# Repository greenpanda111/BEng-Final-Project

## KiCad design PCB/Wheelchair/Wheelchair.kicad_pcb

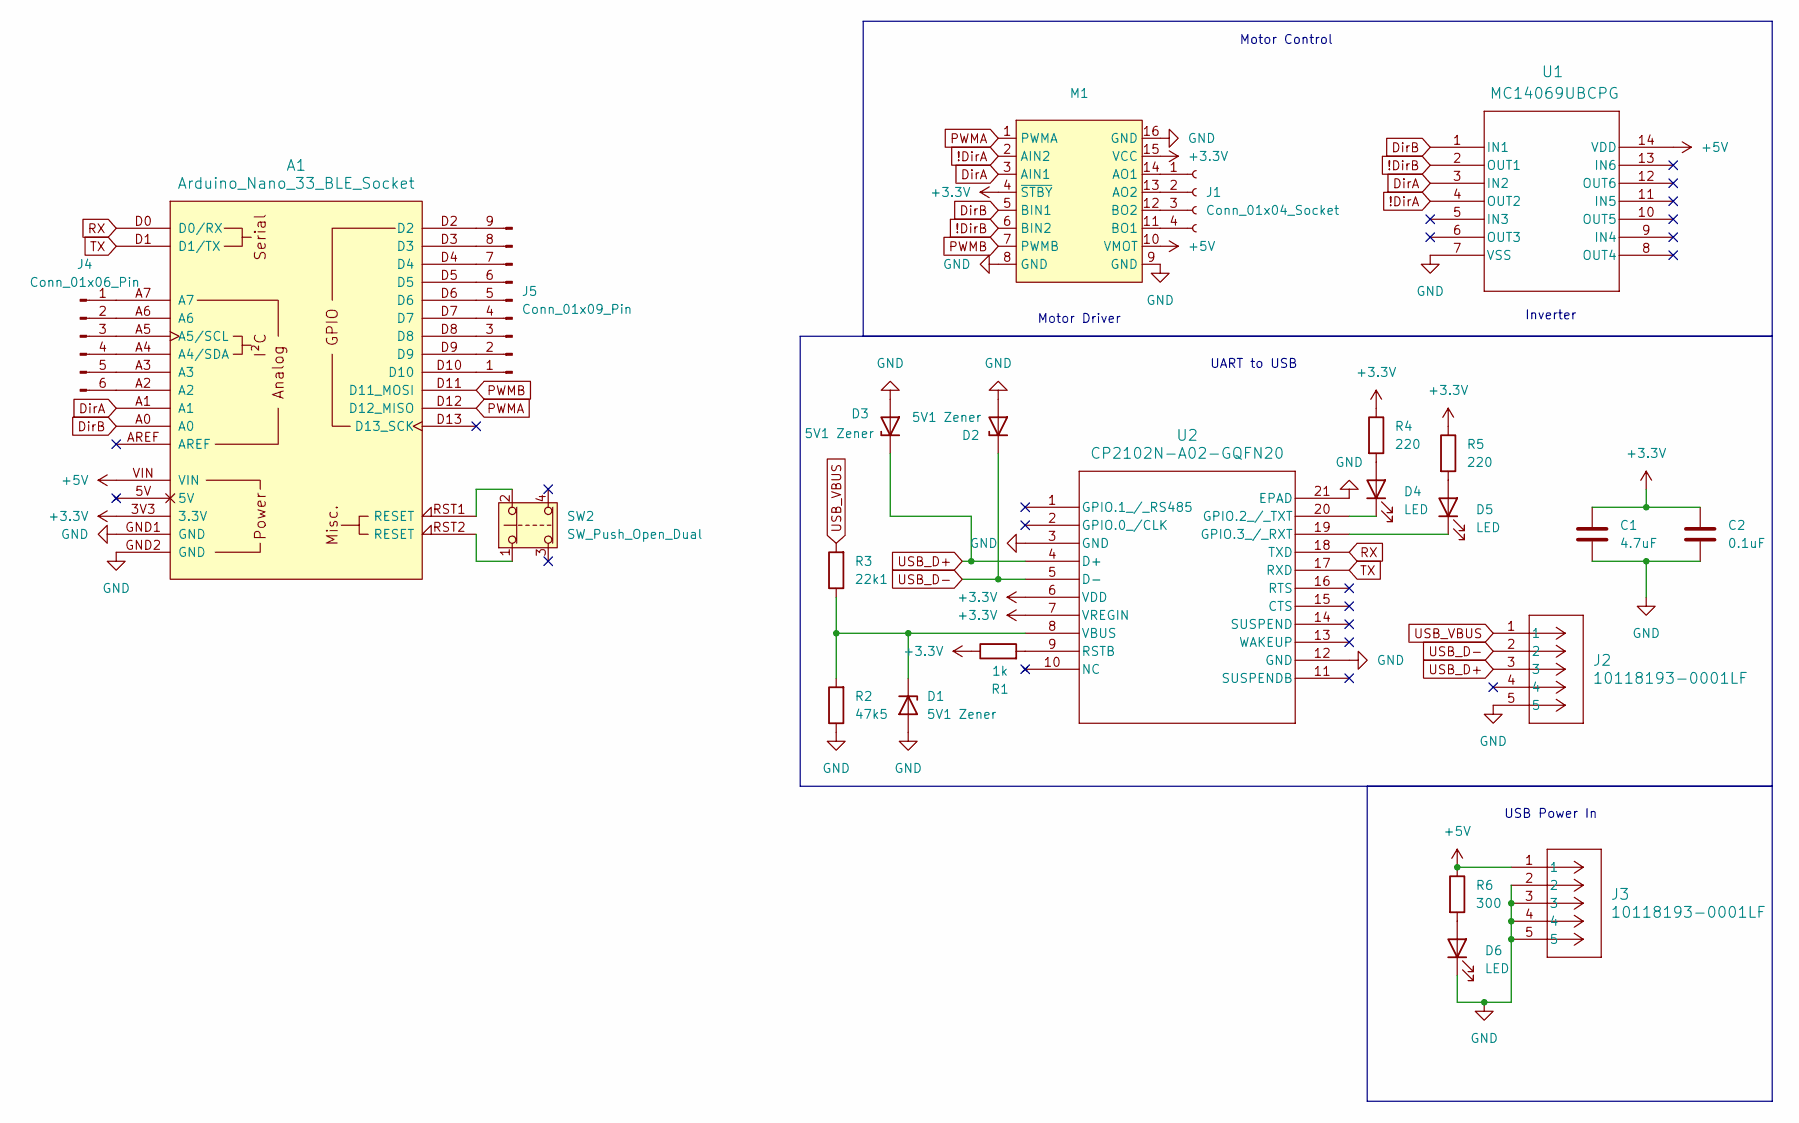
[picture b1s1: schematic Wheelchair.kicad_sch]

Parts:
A1: Arduino_Nano_33_BLE_Socket; Arduino_Nano_Every_Socket
C1: 4.7uF; CP_Radial_D5.0mm_P2.50mm
C2: 0.1uF; C_Disc_D3.8mm_W2.6mm_P2.50mm
D1, D2, D3: 5V1 Zener; D_DO-35_SOD27_P7.62mm_Horizontal
D4, D5, D6: LED; LED_D5.0mm
J1: Conn_01x04_Socket; PinSocket_1x04_P2.54mm_Vertical
J2, J3: 10118193-0001LF; USB_Micro-B_Amphenol_10118193-0001LF_Horizontal
J4: Conn_01x06_Pin; PinHeader_1x06_P2.54mm_Vertical
J5: Conn_01x09_Pin; PinHeader_1x09_P2.54mm_Vertical
M1: Pololu_MD08A_Motor_Driver
R1: 1k; R_Axial_DIN0207_L6.3mm_D2.5mm_P10.16mm_Horizontal
R2: 47k5; R_Axial_DIN0207_L6.3mm_D2.5mm_P10.16mm_Horizontal
R3: 22k1; R_Axial_DIN0207_L6.3mm_D2.5mm_P10.16mm_Horizontal
R4, R5: 220; R_Axial_DIN0207_L6.3mm_D2.5mm_P10.16mm_Horizontal
R6: 300; R_Axial_DIN0207_L6.3mm_D2.5mm_P10.16mm_Horizontal
SW2: SW_Push_Open_Dual; SW_PUSH_6mm_H4.3mm
U1: MC14069UBCPG; PDIP-14_ONS
U2: CP2102N-A02-GQFN20; QFN20_CP2102N_SIL

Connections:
!DirA: M1.2 (AIN2), U1.4 (OUT2)
!DirB: M1.6 (BIN2), U1.2 (OUT1)
+3.3V: A1.3V3 (3.3V), C1.1, C2.1, M1.4 (~STBY), M1.15 (VCC), R1.1, R4.1, R5.1, U2.6 (VDD), U2.7 (VREGIN)
+5V: A1.VIN, J3.1, M1.10 (VMOT), R6.1, U1.14 (VDD)
DirA: A1.A1, M1.3 (AIN1), U1.3 (IN2)
DirB: A1.A0, M1.5 (BIN1), U1.1 (IN1)
GND: A1.GND1 (GND), A1.GND2 (GND), C1.2, C2.2, D1.2 (A), D2.2 (A), D3.2 (A), D6.1 (K), J2.5, J3.2, J3.3, J3.4, J3.5, M1.8 (GND), M1.9 (GND), M1.16 (GND), R2.1, U1.7 (VSS), U2.3 (GND), U2.12 (GND), U2.21 (EPAD)
unnamed: A1.A4 (A4/SDA), J4.4
unnamed: A1.A5 (A5/SCL), J4.3
unnamed: A1.RST1 (RESET), SW2.2
unnamed: A1.RST2 (RESET), SW2.1
unnamed: D1.1 (K), R2.2, R3.1, U2.8 (VBUS)
unnamed: D4.2 (A), R4.2
unnamed: D4.1 (K), U2.20 (GPIO.2_/_TXT)
unnamed: D5.2 (A), R5.2
unnamed: D5.1 (K), U2.19 (GPIO.3_/_RXT)
unnamed: D6.2 (A), R6.2
unnamed: J1.1, M1.14 (AO1)
unnamed: J1.2, M1.13 (AO2)
unnamed: J1.3, M1.12 (BO2)
unnamed: J1.4, M1.11 (BO1)
unnamed: A1.A7, J4.1
unnamed: A1.A6, J4.2
unnamed: A1.A3, J4.5
unnamed: A1.A2, J4.6
unnamed: A1.D10, J5.1
unnamed: A1.D9, J5.2
unnamed: A1.D8, J5.3
unnamed: A1.D7, J5.4
unnamed: A1.D6, J5.5
unnamed: A1.D5, J5.6
unnamed: A1.D4, J5.7
unnamed: A1.D3, J5.8
unnamed: A1.D2, J5.9
unnamed: R1.2, U2.9 (RSTB)
PWMA: A1.D12 (D12_MISO), M1.1 (PWMA)
PWMB: A1.D11 (D11_MOSI), M1.7 (PWMB)
RX: A1.D0 (D0/RX), U2.18 (TXD)
TX: A1.D1 (D1/TX), U2.17 (RXD)
USB_D+: D3.1 (K), J2.3, U2.4 (D+)
USB_D-: D2.1 (K), J2.2, U2.5 (D-)
USB_VBUS: J2.1, R3.2

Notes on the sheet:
Motor Control
USB Power In
Motor Driver
UART to USB
Inverter

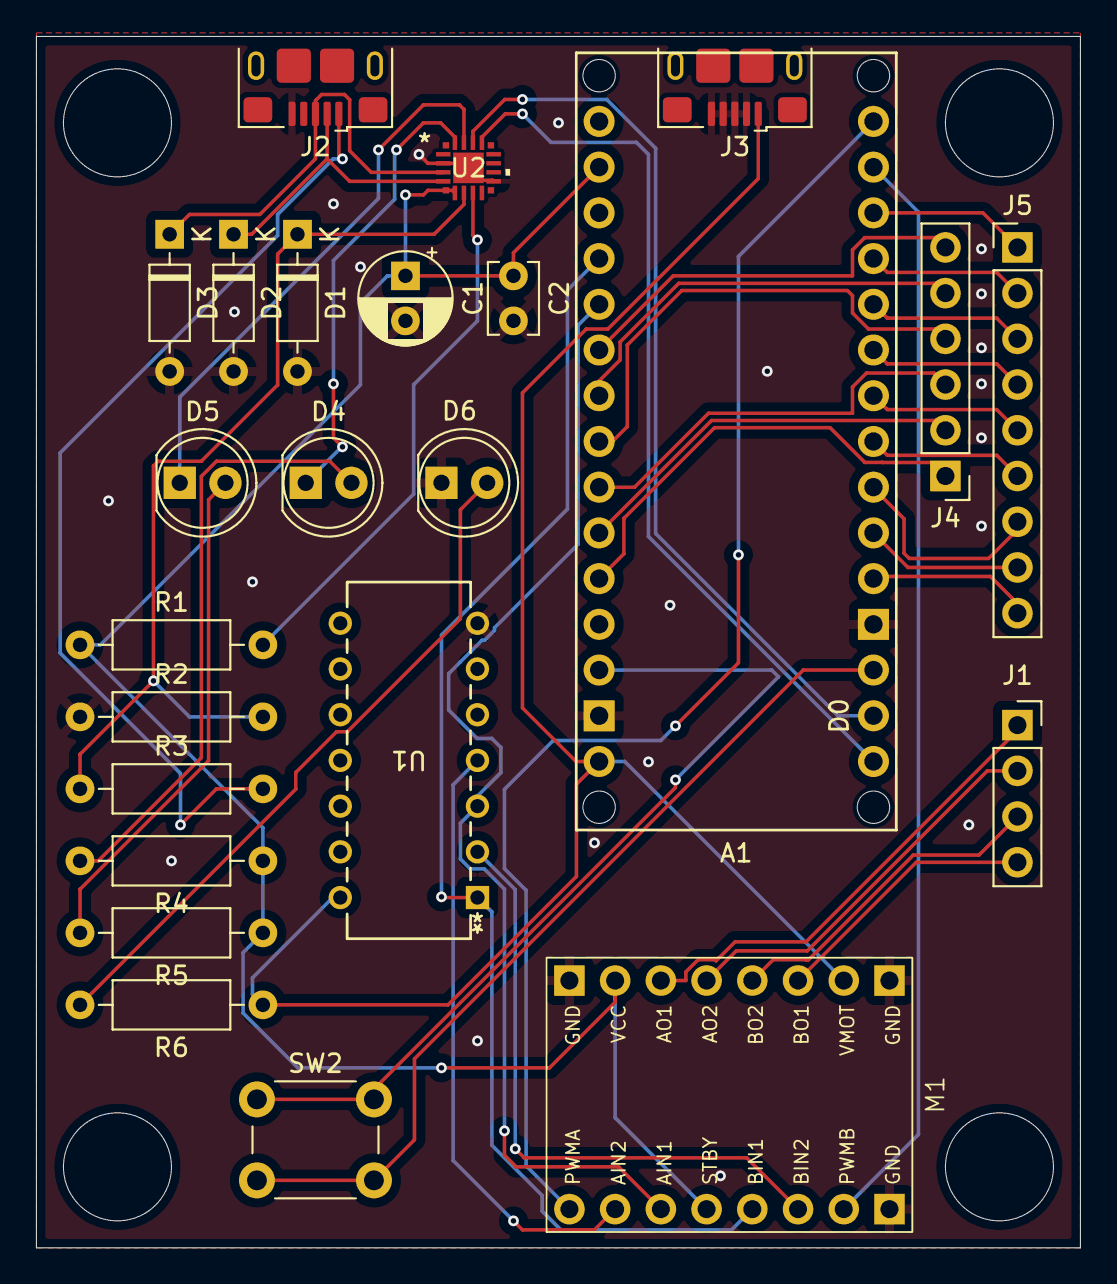
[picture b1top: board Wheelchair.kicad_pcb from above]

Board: 2 copper layers, 58.0 x 67.3 mm, 24 parts (0 on the bottom side), 42 nets.

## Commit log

2025-03-24 BLE Controller
2025-03-24 RF Controller
2025-03-24 BLE Toy
2025-03-25 Joystick Implementation
2025-03-26 Lora Controller
2025-03-26 LoRa comms structure - not working
2025-04-02 Removed RF files
2025-04-02 ESp controller
2025-04-02 Wheelchair Serial Control
2025-04-02 Pi Scripts Added
2025-04-03 Wheelchair PCB schematic
2025-04-03 PWM pin update
2025-04-03 PCB_Layout
2025-04-03 PCB_routed
2025-04-16 PWM Pins re-assigned
2025-04-25 PCB Pins
2025-04-26 Pins and motor speed changed
2025-04-27 Serial debugging removed
2025-04-28 Mode Switching
2025-04-28 Pi Mode Switching
2025-04-28 Arduino Mode Switching
2025-04-28 Naming Conflicts resolved
2025-04-28 Control Update
2025-04-28 Code commented for debugging
2025-04-28 Packed header decoding
2025-04-29 serialise data
2025-04-29 Headers
2025-04-29 Arduino Header
2025-05-01 Joystick Comms
2025-05-01 serialisation
2025-05-02 Joystick deadzone
2025-05-21 Demo folder
2025-05-21 RPi basic demo
2025-05-21 esp,arduino demo code
